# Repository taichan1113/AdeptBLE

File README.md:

## Handsolderable version of Ploopy Adept BLE modification

Original work forked from : https://github.com/taichan1113/AdeptBLE

# Excuse

AdeptBLE is a great idea, but it uses 0603 components, I wanted to use 0806 as they are more managable, and easy to handsoler

## electronics

Designed by KiCAD and produted by [JLCPCB](https://jlcpcb.com/)

Basically you need XIAO nRF52840 board, PMW3610 optical sensor, omron D2LS-21 mouse switch, 6-pin slide switch and battery.

Other parts are set as below.

TODO - Provide updated BOM

## firmware (Stock firmware from taichan1113 will work)

Here includes uf2 file built by zmk.

You can find the code [here](https://github.com/taichan1113/mouse-test/tree/main).

## housing

I updated the houseing to support the pcb better, and have cutout for battery wire below the pcb to avoid any mis-alignment.

## NOTE: 

Desin are not tested in very depth, i created one single prototype which is working without issues, YMMV. reach out in case you find issues or open PR.

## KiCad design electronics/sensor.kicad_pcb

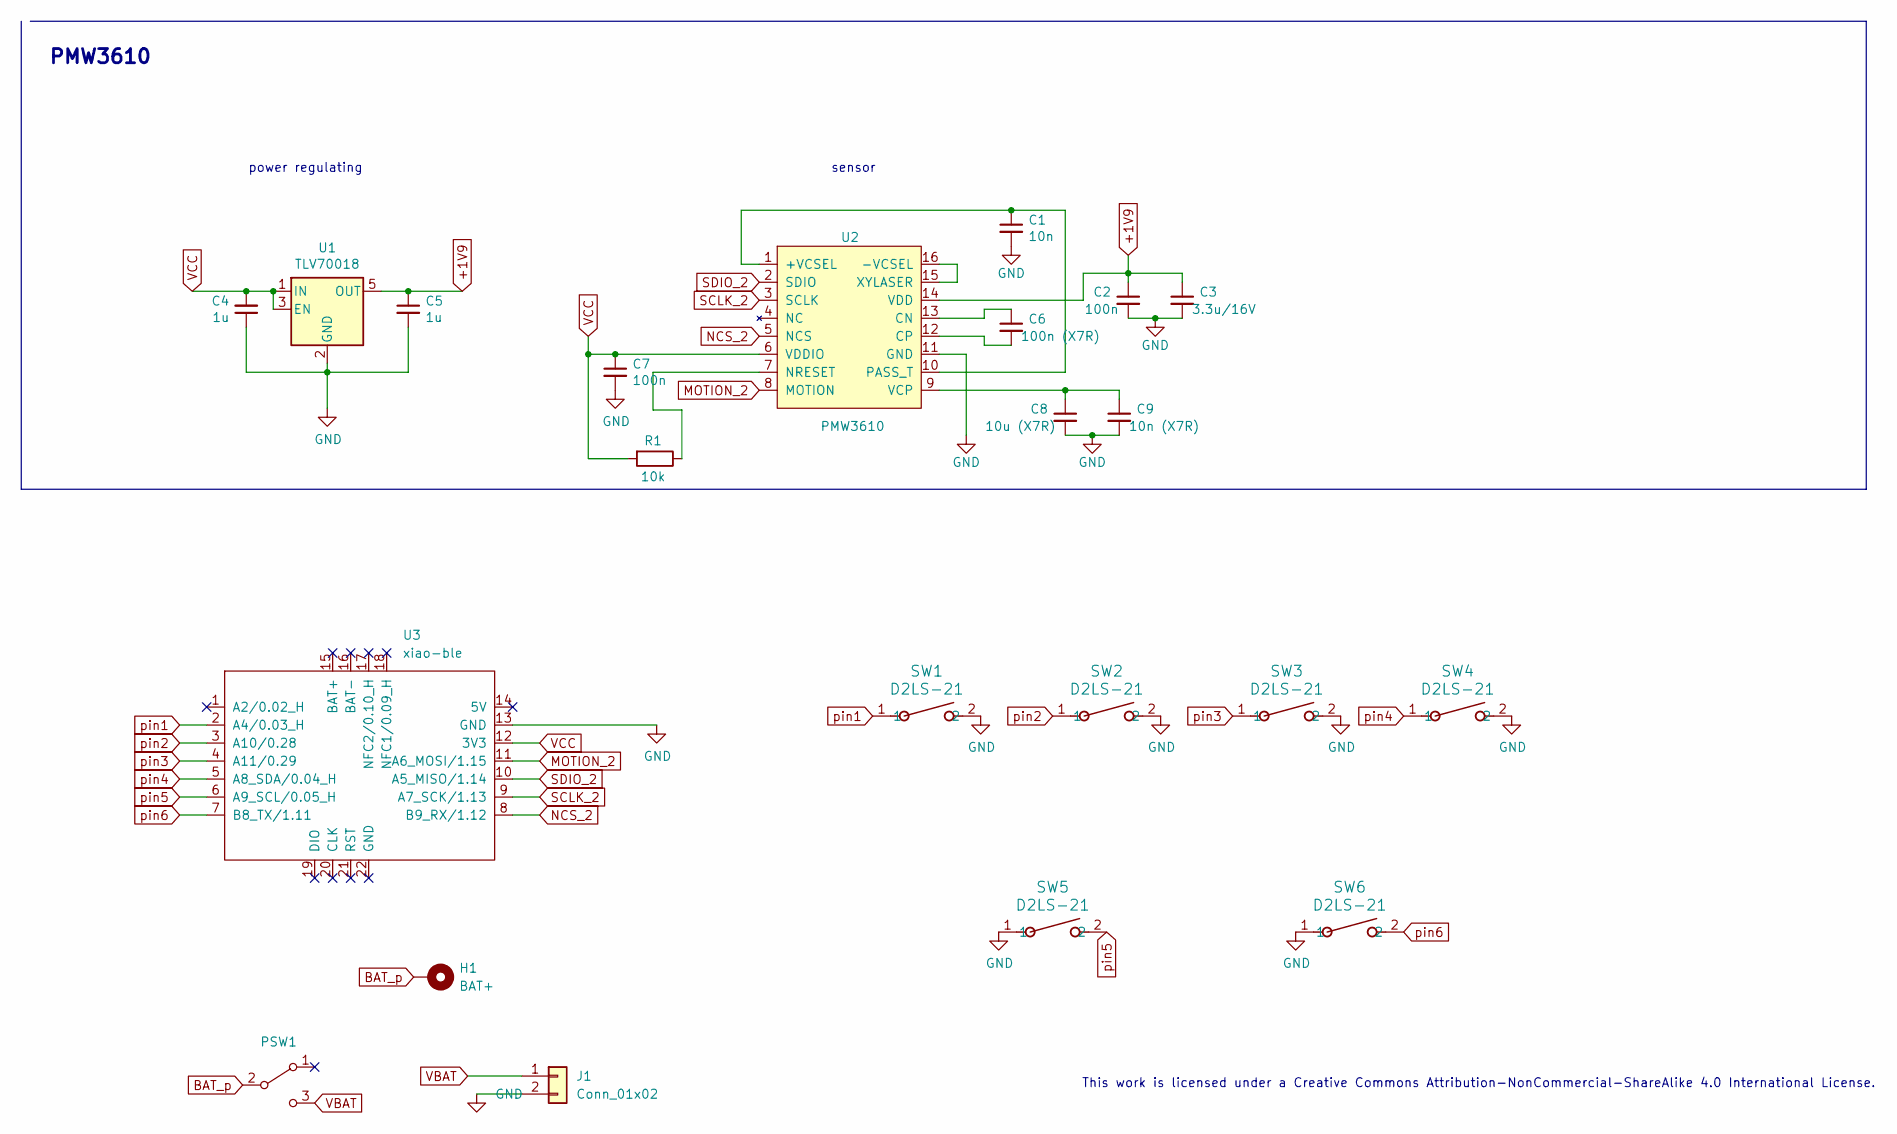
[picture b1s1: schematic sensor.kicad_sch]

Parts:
C1: 10n; C_0805_2012Metric_Pad1.18x1.45mm_HandSolder; LCSC C19666
C2, C7: 100n; C_0805_2012Metric_Pad1.18x1.45mm_HandSolder; LCSC C19666
C3: 3.3u/16V; C_0805_2012Metric_Pad1.18x1.45mm_HandSolder; LCSC C19666
C4: 1u; C_0805_2012Metric_Pad1.18x1.45mm_HandSolder; LCSC C14663
C5: 1u; C_0805_2012Metric_Pad1.18x1.45mm_HandSolder; LCSC C15849
C6: 100n (X7R); C_0805_2012Metric_Pad1.18x1.45mm_HandSolder; LCSC C19666
C8: 10u (X7R); C_0805_2012Metric_Pad1.18x1.45mm_HandSolder; LCSC C19666
C9: 10n (X7R); C_0805_2012Metric_Pad1.18x1.45mm_HandSolder; LCSC C19666
H1: BAT+; PinSocket_1x01_P2.00mm_Vertical
J1: Conn_01x02; Battery_2pin
PSW1: SW_SPDT; TGSW_MSK-12D19
R1: 10k; C_0805_2012Metric_Pad1.18x1.45mm_HandSolder
SW1, SW2, SW3, SW4, SW5, SW6: D2LS-21; SW_D2LS-11_2_OMR
U1: TLV70018; SOT-23-5_HandSoldering; LCSC C146366
U2: PMW3610
U3: xiao-ble; XIAO-nRF52840-SMD_flipped

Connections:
+1V9: C2.1, C3.1, C5.1, U1.5 (OUT), U2.14 (VDD)
BAT_p: H1.1, PSW1.2 (B)
GND: C1.2, C2.2, C3.2, C4.1, C5.2, C7.2, C8.2, C9.2, J1.2, SW1.2, SW2.2, SW3.2, SW4.2, SW5.1, SW6.1, U1.2 (GND), U1.4 (NC), U2.11 (GND), U3.13 (GND)
MOTION_2: U2.8 (MOTION), U3.11 (A6_MOSI/1.15)
NCS_2: U2.5 (NCS), U3.8 (B9_RX/1.12)
unnamed: C1.1, U2.1 (+VCSEL), U2.10 (PASS_T)
unnamed: U2.15 (XYLASER), U2.16 (-VCSEL)
unnamed: C6.1, U2.13 (CN)
unnamed: C6.2, U2.12 (CP)
unnamed: R1.1, U2.7 (NRESET)
unnamed: C8.1, C9.1, U2.9 (VCP)
SCLK_2: U2.3 (SCLK), U3.9 (A7_SCK/1.13)
SDIO_2: U2.2 (SDIO), U3.10 (A5_MISO/1.14)
VBAT: J1.1, PSW1.3 (C)
VCC: C4.2, C7.1, R1.2, U1.1 (IN), U1.3 (EN), U2.6 (VDDIO), U3.12 (3V3)
pin1: SW1.1, U3.2 (A4/0.03_H)
pin2: SW2.1, U3.3 (A10/0.28)
pin3: SW3.1, U3.4 (A11/0.29)
pin4: SW4.1, U3.5 (A8_SDA/0.04_H)
pin5: SW5.2, U3.6 (A9_SCL/0.05_H)
pin6: SW6.2, U3.7 (B8_TX/1.11)

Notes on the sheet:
This work is licensed under a Creative Commons Attribution-NonCommercial-ShareAlike 4.0 International License.
sensor
PMW3610
power regulating

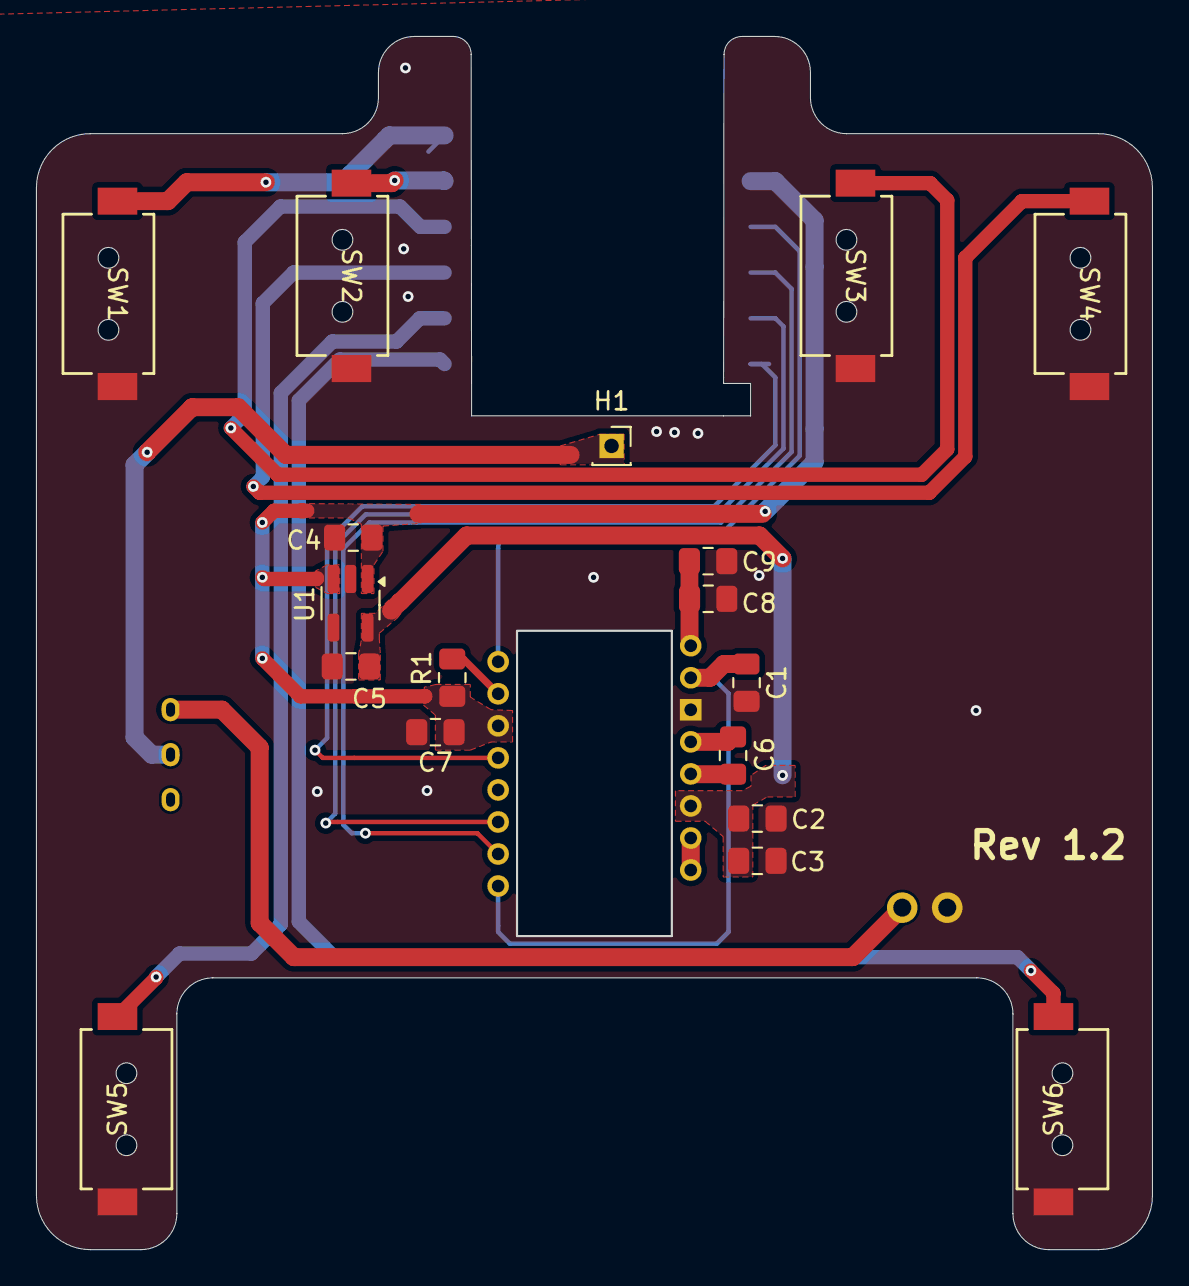
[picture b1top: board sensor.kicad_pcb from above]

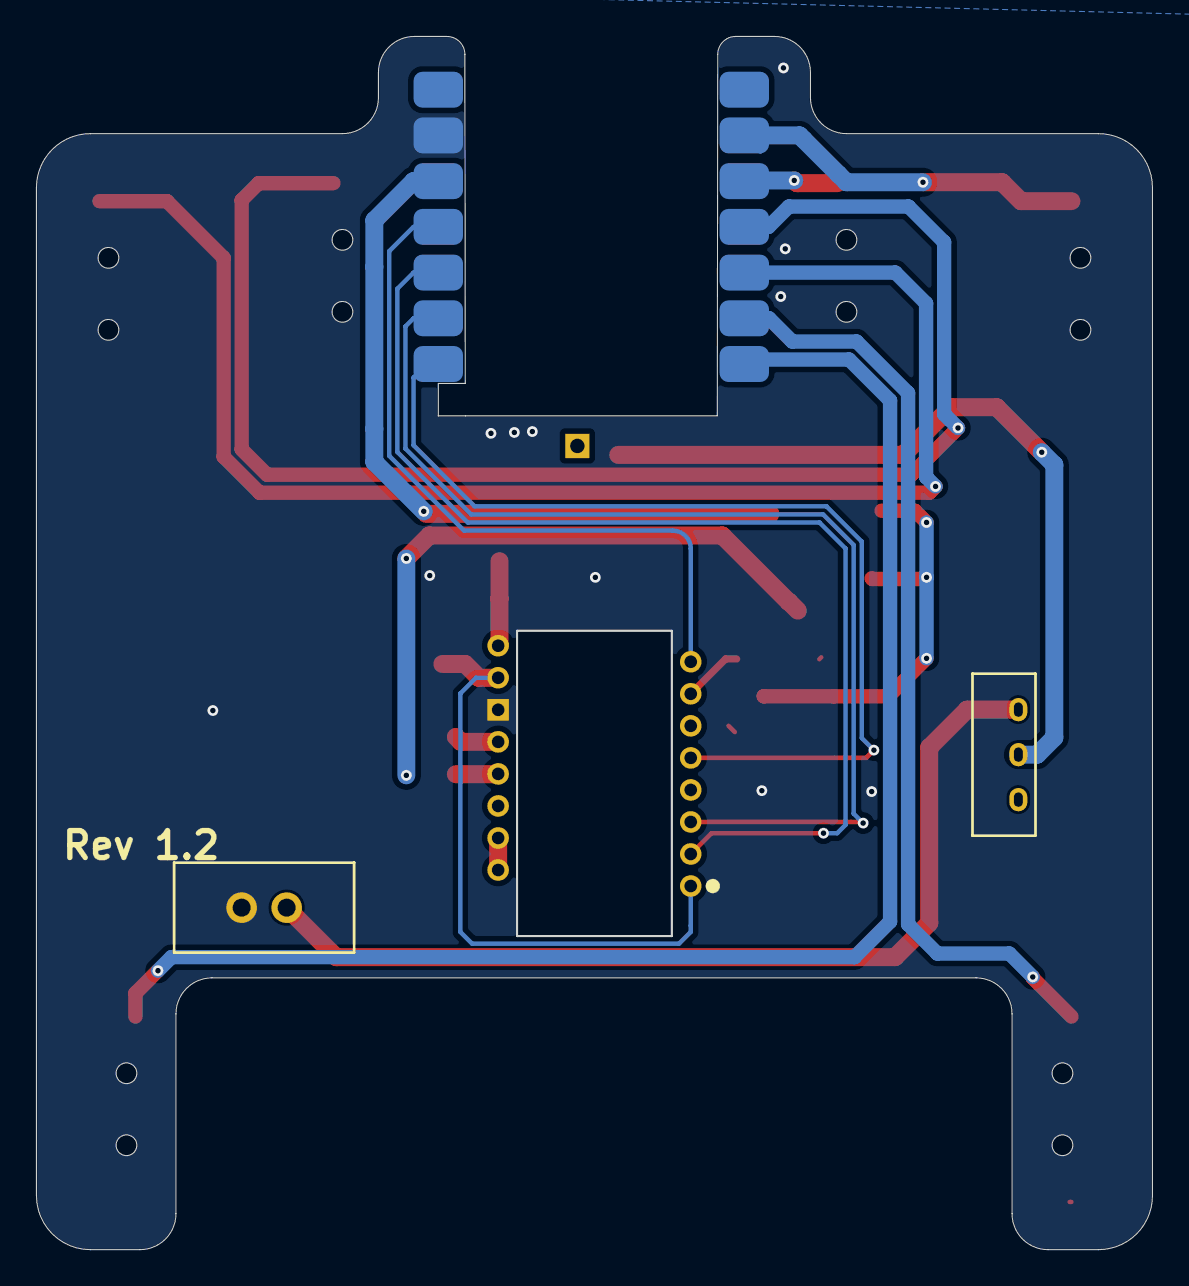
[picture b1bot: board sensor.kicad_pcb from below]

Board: 2 copper layers, 62.0 x 67.4 mm, 22 parts (3 on the bottom side), 21 nets.

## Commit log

2024-08-27 add firmware uf2
2024-08-27 add readme
2024-08-27 add lisence
2024-10-13 update: README
2025-04-01 bottom case step file uploaded
2025-04-02 submodule updated
2026-02-06 handsolder upload
2026-04-05 update file and houseing
2026-05-01 increase trace thickness, and improve fill zones

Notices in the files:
electronics/sensor.kicad_sch:
Copyright Quentin Lebastard
